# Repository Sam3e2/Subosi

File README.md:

# Subosi

## What is this?

An alternative interface board to bluetooth mesh smart touch panel controllers. Touch actions are simulated over the I2C interface. Switches can be connected at the terminal or IDC header.

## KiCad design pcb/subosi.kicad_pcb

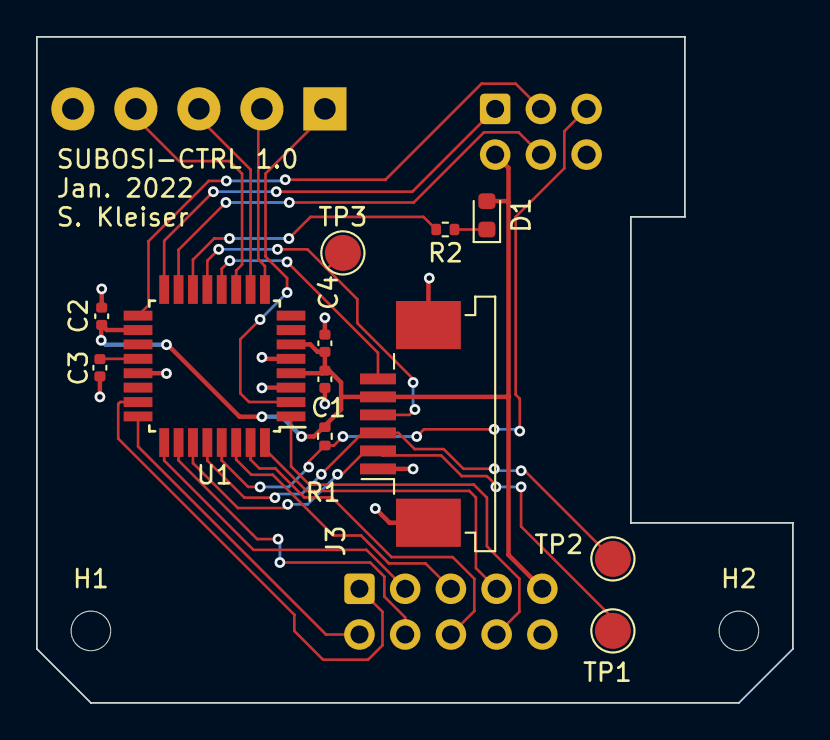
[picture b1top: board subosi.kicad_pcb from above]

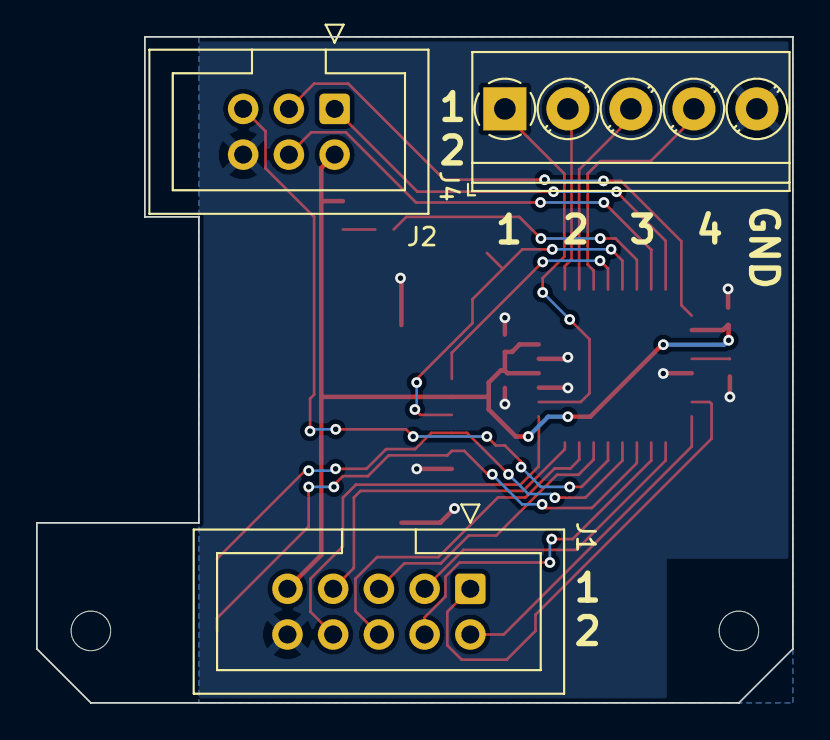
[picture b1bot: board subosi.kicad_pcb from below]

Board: 2 copper layers, 42.0 x 37.0 mm, 17 parts (3 on the bottom side), 25 nets.

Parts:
C1, C2, C3: 100n; C_0402_1005Metric
C4: 10u; C_0402_1005Metric
D1: LED; LED_0603_1608Metric
H1, H2: MountingHole; MountingHole_2.2mm_M2_ISO14580
J1: IO; IDC-Header_2x05_P2.54mm_Vertical
J2: AVR-ISP-6; IDC-Header_2x03_P2.54mm_Vertical
J3: Conn_01x06_MountingPin; TE_84953-6_1x06-1MP_P1.0mm_Horizontal
J4: IN; TerminalBlock_Phoenix_PT-1,5-5-3.5-H_1x05_P3.50mm_Horizontal
R1: 10k; R_0402_1005Metric
R2: 220; R_0402_1005Metric
TP1, TP2, TP3: TestPoint; TestPoint_Pad_D2.0mm
U1: ATmega48-20A; TQFP-32_7x7mm_P0.8mm

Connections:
/LED: J3.6, U1.12 (PB0)
/RST: J2.5 (~RST), R1.1, U1.29 (~RESET/PC6)
/SCL: J3.3, TP2.1, U1.28 (PC5)
/SDA: J3.2, TP1.1, U1.27 (PC4)
/WKUP: J3.4, TP3.1, U1.13 (PB1)
GND: C1.2, C2.2, C3.2, C4.2, J1.10, J2.6 (GND), J3.1, J3.MP (MountPin), J4.5, U1.3 (GND), U1.5 (GND), U1.21 (GND)
unnamed: C3.1, U1.20 (AREF)
unnamed: D1.1 (K), R2.1
unnamed: J1.1, U1.23 (PC0)
unnamed: J1.2, U1.24 (PC1)
unnamed: J1.3, U1.25 (PC2)
unnamed: J1.4, U1.26 (PC3)
unnamed: J1.5, U1.30 (PD0)
unnamed: J1.6, U1.31 (PD1)
unnamed: J1.7, U1.32 (PD2)
unnamed: J1.8, U1.1 (PD3)
unnamed: J2.1 (MISO), U1.16 (PB4)
unnamed: J2.3 (SCK), U1.17 (PB5)
unnamed: J2.4 (MOSI), U1.15 (PB3)
unnamed: J4.1, U1.2 (PD4)
unnamed: J4.2, U1.9 (PD5)
unnamed: J4.3, U1.10 (PD6)
unnamed: J4.4, U1.11 (PD7)
unnamed: R2.2, U1.14 (PB2)
VCC: C1.1, C2.1, C4.1, D1.2 (A), J1.9, J2.2 (VCC), J3.5, R1.2, U1.4 (VCC), U1.6 (VCC), U1.18 (AVCC)

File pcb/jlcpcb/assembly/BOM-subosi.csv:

Comment,Designator,Footprint,LCSC
ATmega48-20A,U1,TQFP-32_7x7mm_P0.8mm,C111451
LED,D1,LED_0603_1608Metric,C2286
220,R2,R_0402_1005Metric,C25091
10k,R1,R_0402_1005Metric,C25744
Conn_01x06_MountingPin,J3,TE_84953-6_1x06-1MP_P1.0mm_Horizontal,C262712
100n,"C1,C2,C3,C4",C_0402_1005Metric,C52923
IO,J1,IDC-Header_2x05_P2.54mm_Vertical,
MountingHole,H1,MountingHole_2.2mm_M2_ISO14580,
AVR-ISP-6,J2,IDC-Header_2x03_P2.54mm_Vertical,
MountingHole,H2,MountingHole_2.2mm_M2_ISO14580,
IN,J4,"TerminalBlock_Phoenix_PT-1,5-5-3.5-H_1x05_P3.50mm_Horizontal",
TestPoint,TP3,TestPoint_Pad_D2.0mm,
TestPoint,TP2,TestPoint_Pad_D2.0mm,
TestPoint,TP1,TestPoint_Pad_D2.0mm,

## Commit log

2022-01-26 fixed group2
2022-01-26 long press action for Pin 3/4
